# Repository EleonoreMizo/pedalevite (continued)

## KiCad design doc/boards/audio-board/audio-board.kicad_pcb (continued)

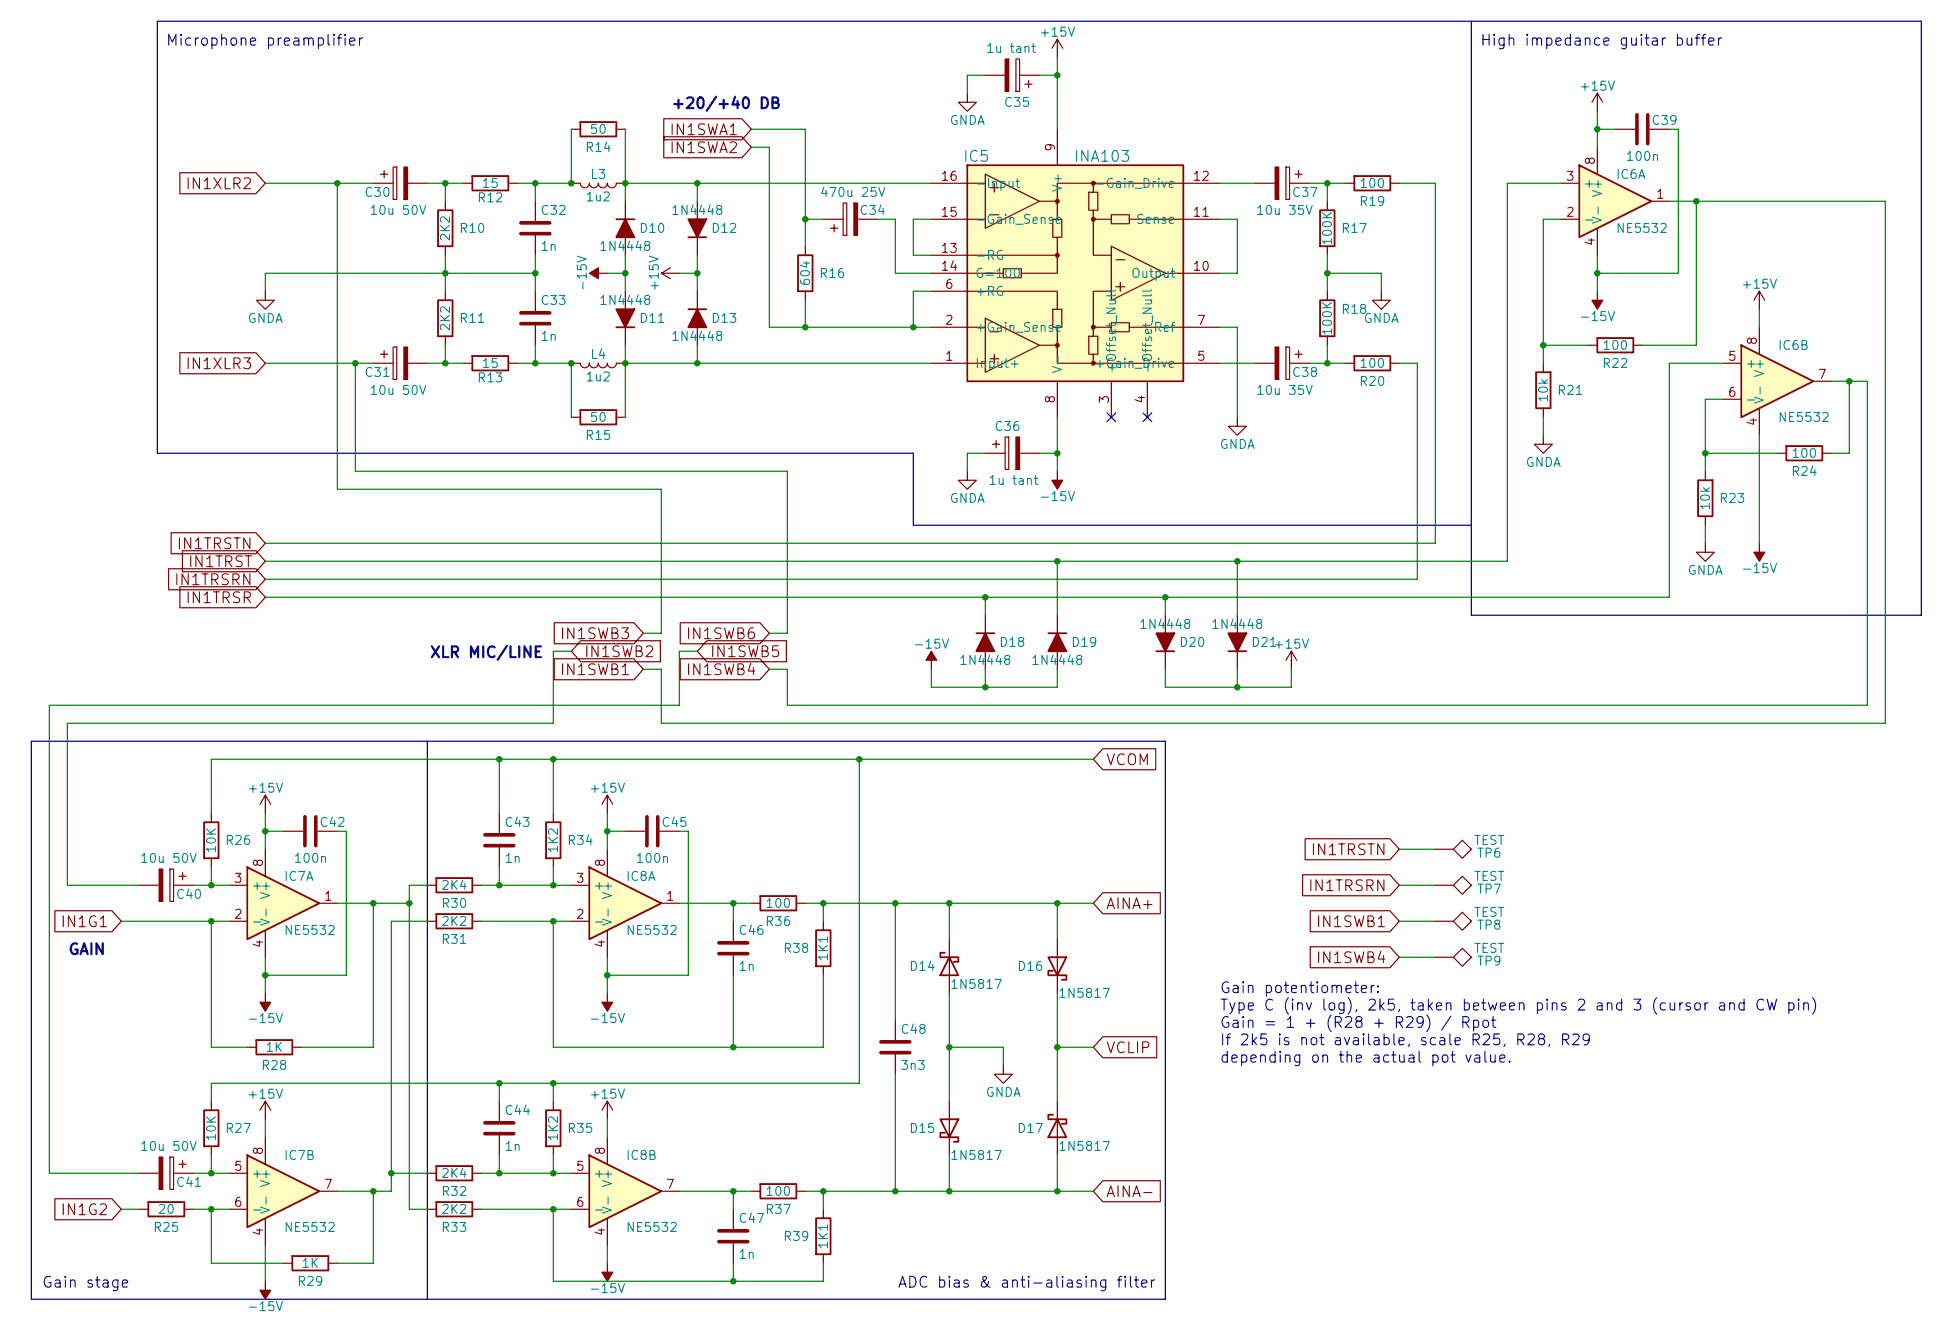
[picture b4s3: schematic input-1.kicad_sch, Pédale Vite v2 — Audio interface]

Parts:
C30, C31, C40, C41: 10u 50V; CP_Radial_D8.0mm_P3.50mm
C32, C33: 1n; C_Rect_L7.2mm_W4.5mm_P5.00mm_FKS2_FKP2_MKS2_MKP2
C34: 470u 25V; CP_Radial_D10.0mm_P5.00mm
C35, C36: 1u tant; CP_Radial_D5.0mm_P2.50mm
C37, C38: 10u 35V; CP_Radial_D5.0mm_P2.00mm
C39, C42, C45: 100n; C_Disc_D3.4mm_W2.1mm_P2.50mm
C43, C44, C46, C47: 1n; C_Disc_D6.0mm_W2.5mm_P5.00mm
C48: 3n3; C_Disc_D6.0mm_W2.5mm_P5.00mm
D10, D11, D12, D13, D18, D19, D20, D21: 1N4448; D_DO-35_SOD27_P7.62mm_Horizontal
D14, D15, D16, D17: 1N5817; D_DO-35_SOD27_P7.62mm_Horizontal
IC5: INA103; DIP-16_W7.62mm_Socket
IC6, IC7, IC8: NE5532; DIP-8_W7.62mm_Socket
L3, L4: 1u2; R_Axial_DIN0309_L9.0mm_D3.2mm_P5.08mm_Vertical
R10, R11, R31, R33: 2K2; R_Axial_DIN0207_L6.3mm_D2.5mm_P7.62mm_Horizontal
R12, R13: 15; R_Axial_DIN0207_L6.3mm_D2.5mm_P7.62mm_Horizontal
R14, R15: 50; R_Axial_DIN0207_L6.3mm_D2.5mm_P7.62mm_Horizontal
R16: 604; R_Axial_DIN0207_L6.3mm_D2.5mm_P7.62mm_Horizontal
R17, R18: 100K; R_Axial_DIN0207_L6.3mm_D2.5mm_P7.62mm_Horizontal
R19, R20, R22, R24, R36, R37: 100; R_Axial_DIN0207_L6.3mm_D2.5mm_P7.62mm_Horizontal
R21, R23: 10k; R_Axial_DIN0207_L6.3mm_D2.5mm_P7.62mm_Horizontal
R25: 20; R_Axial_DIN0207_L6.3mm_D2.5mm_P7.62mm_Horizontal
R26, R27: 10K; R_Axial_DIN0207_L6.3mm_D2.5mm_P7.62mm_Horizontal
R28, R29: 1K; R_Axial_DIN0207_L6.3mm_D2.5mm_P7.62mm_Horizontal
R30, R32: 2K4; R_Axial_DIN0207_L6.3mm_D2.5mm_P7.62mm_Horizontal
R34, R35: 1K2; R_Axial_DIN0207_L6.3mm_D2.5mm_P7.62mm_Horizontal
R38, R39: 1K1; R_Axial_DIN0207_L6.3mm_D2.5mm_P7.62mm_Horizontal
TP6, TP7, TP8, TP9: TEST; Measurement_Point_Round-TH_Small

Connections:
-15V: C36.2, C39.2, C42.2, C45.2, D10.2 (A), D11.2 (A), D18.2 (A), D19.2 (A), IC5.8 (V-), IC6.4 (V-), IC7.4 (V-), IC8.4 (V-); also elsewhere on the board
AINA+: C48.1, D14.1 (K), D16.2 (A), R36.1, R38.1; also elsewhere on the board
AINA-: C48.2, D15.1 (K), D17.2 (A), R37.1, R39.1; also elsewhere on the board
GNDA: C32.2, C33.1, C35.2, C36.1, D14.2 (A), D15.2 (A), IC5.7 (Ref), R10.2, R11.1, R17.2, R18.1, R21.1, R23.1; also elsewhere on the board
IN1G1: IC7.2 (-), R28.2; also elsewhere on the board
IN1G2: R25.2; also elsewhere on the board
IN1SWA1: C34.1, R16.1; also elsewhere on the board
IN1SWA2: IC5.2 (+Gain_Sense), IC5.6 (+RG), R16.2; also elsewhere on the board
IN1SWB1: IC6.1, R22.1, TP8.1; also elsewhere on the board
IN1SWB2: C40.2; also elsewhere on the board
IN1SWB3: C30.1; also elsewhere on the board
IN1SWB4: IC6.7, R24.1, TP9.1; also elsewhere on the board
IN1SWB5: C41.2; also elsewhere on the board
IN1SWB6: C31.1; also elsewhere on the board
IN1TRSR: D18.1 (K), D20.2 (A), IC6.5 (+); also elsewhere on the board
IN1TRSRN: R20.1, TP7.1; also elsewhere on the board
IN1TRST: D19.1 (K), D21.2 (A), IC6.3 (+); also elsewhere on the board
IN1TRSTN: R19.1, TP6.1; also elsewhere on the board
unnamed: C30.2, R10.1, R12.2
unnamed: C31.2, R11.2, R13.2
unnamed: C32.1, L3.2, R12.1, R14.2
unnamed: C33.2, L4.2, R13.1, R15.2
unnamed: C34.2, IC5.14 (G=100)
unnamed: C37.1, R17.1, R19.2
unnamed: C37.2, IC5.12 (-Gain_Drive)
unnamed: C38.1, R18.2, R20.2
unnamed: C38.2, IC5.5 (+Gain_Drive)
unnamed: C40.1, IC7.3 (+), R26.2
unnamed: C41.1, IC7.5 (+), R27.2
unnamed: C43.2, IC8.3 (+), R30.1, R34.2
unnamed: C44.2, IC8.5 (+), R32.1, R35.2
unnamed: C46.1, IC8.1, R36.2
unnamed: C46.2, IC8.2 (-), R31.1, R38.2
unnamed: C47.1, IC8.7, R37.2
unnamed: C47.2, IC8.6 (-), R33.1, R39.2
unnamed: D10.1 (K), D12.2 (A), IC5.16 (-Input), L3.1, R14.1
unnamed: D11.1 (K), D13.2 (A), IC5.1 (Input+), L4.1, R15.1
unnamed: IC5.10 (Output), IC5.11 (Sense)
unnamed: IC5.13 (-RG), IC5.15 (-Gain_Sense)
unnamed: IC6.2 (-), R21.2, R22.2
unnamed: IC6.6 (-), R23.2, R24.2
unnamed: IC7.1, R28.1, R30.2, R33.2
unnamed: IC7.6 (-), R25.1, R29.2
unnamed: IC7.7, R29.1, R31.2, R32.2
VCLIP: D16.1 (K), D17.1 (K); also elsewhere on the board
VCOM: C43.1, C44.1, R26.1, R27.1, R34.1, R35.1; also elsewhere on the board

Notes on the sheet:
High impedance guitar buffer
Gain stage
+20/+40 DB
XLR MIC/LINE
Gain potentiometer: Type C (inv log), 2k5, taken between pins 2 and 3 (cursor and CW pin) Gain = 1 + (R28 + R29) / Rpot If 2k5 is not available, scale R25, R28, R29 depending on the actual pot value.
Microphone preamplifier
ADC bias & anti-aliasing filter
GAIN

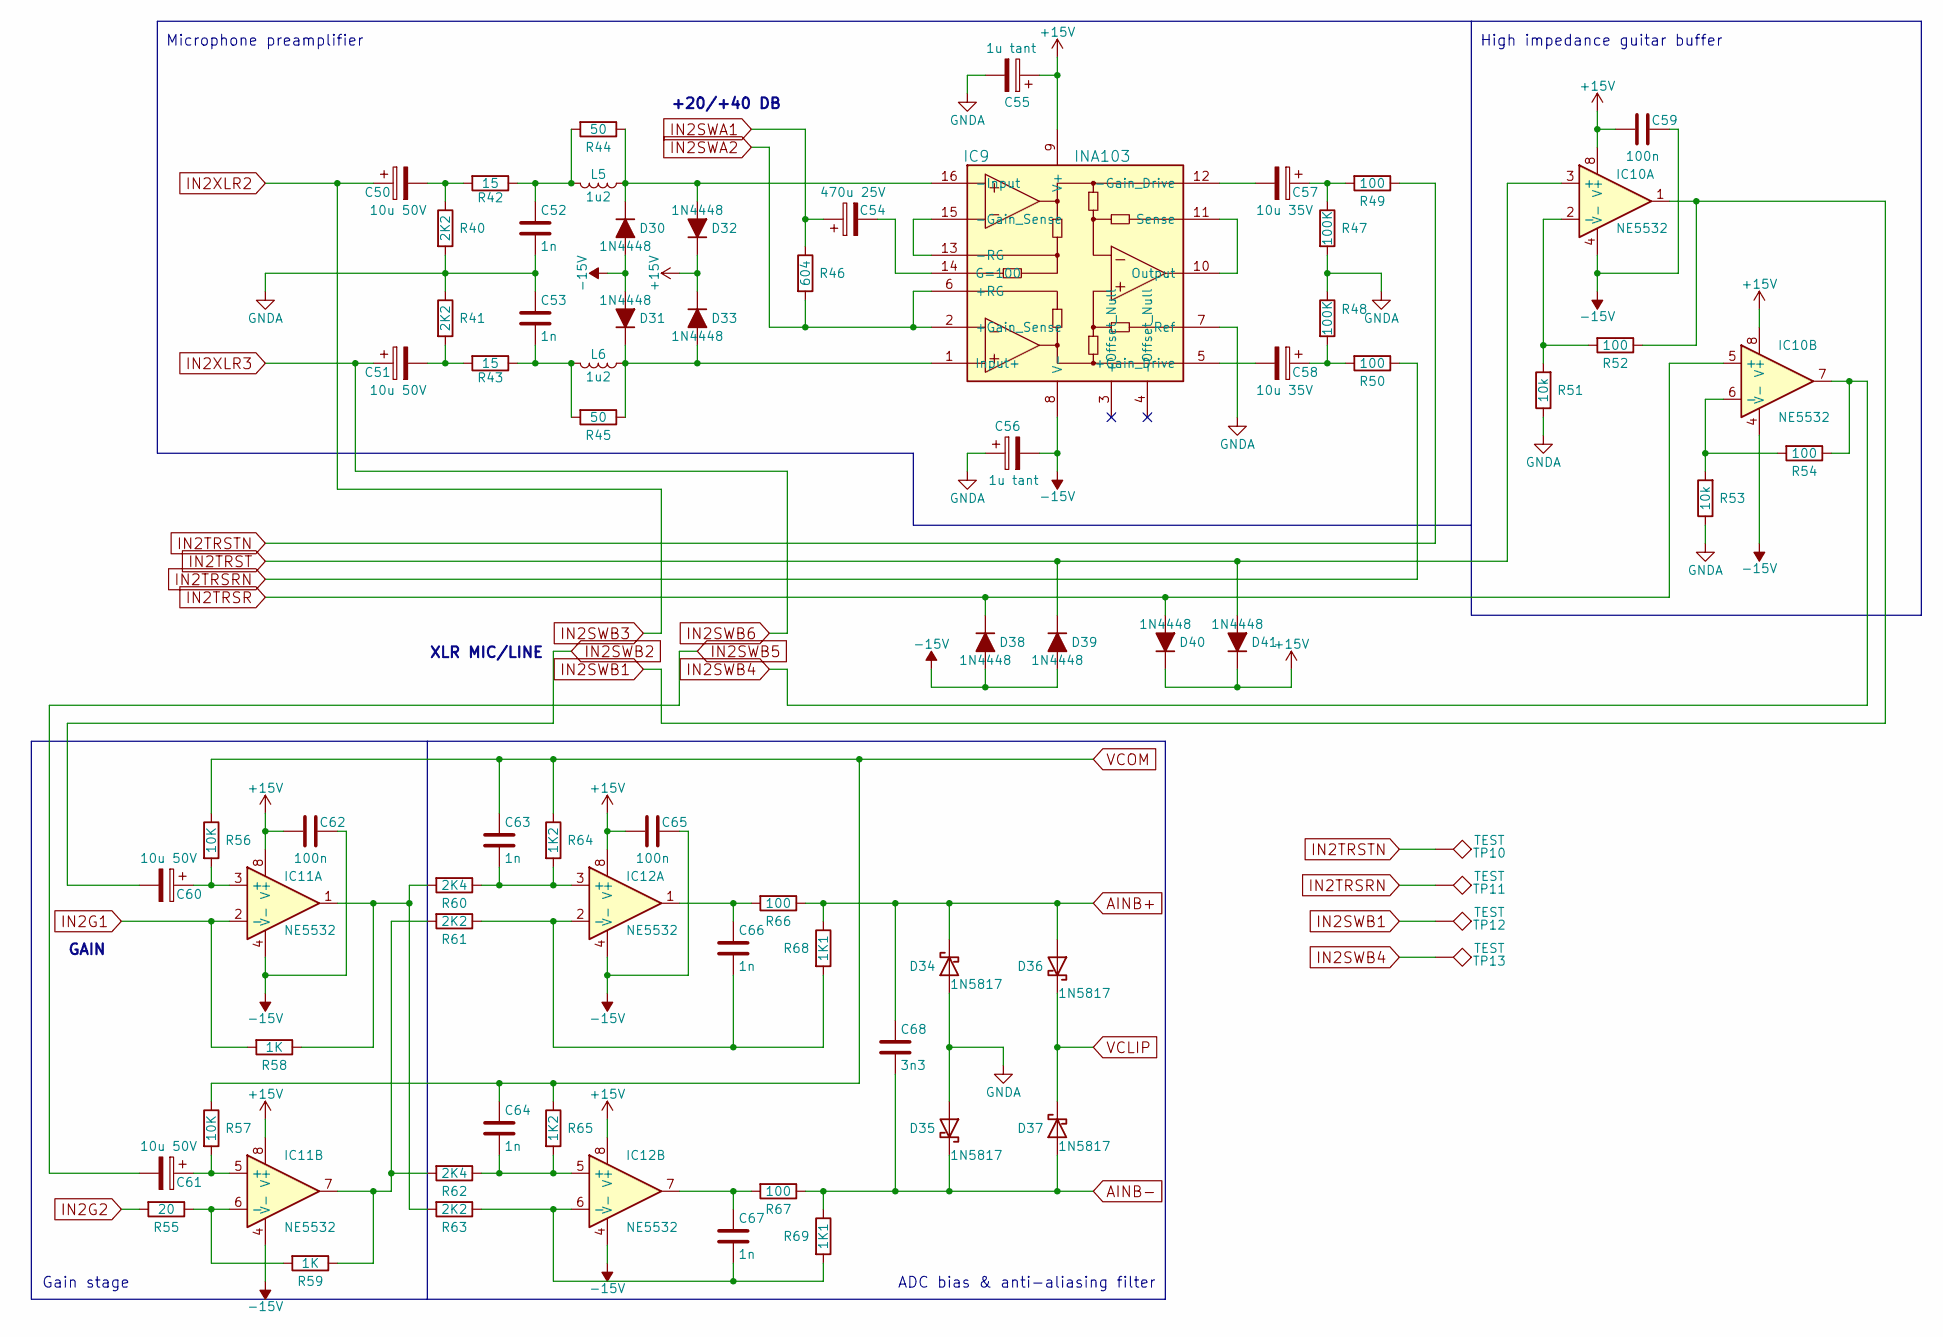
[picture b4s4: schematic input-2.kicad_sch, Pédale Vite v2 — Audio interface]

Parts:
C50, C51, C60, C61: 10u 50V; CP_Radial_D8.0mm_P3.50mm
C52, C53: 1n; C_Rect_L7.2mm_W4.5mm_P5.00mm_FKS2_FKP2_MKS2_MKP2
C54: 470u 25V; CP_Radial_D10.0mm_P5.00mm
C55, C56: 1u tant; CP_Radial_D5.0mm_P2.50mm
C57, C58: 10u 35V; CP_Radial_D5.0mm_P2.00mm
C59, C62, C65: 100n; C_Disc_D3.4mm_W2.1mm_P2.50mm
C63, C64, C66, C67: 1n; C_Disc_D6.0mm_W2.5mm_P5.00mm
C68: 3n3; C_Disc_D6.0mm_W2.5mm_P5.00mm
D30, D31, D32, D33, D38, D39, D40, D41: 1N4448; D_DO-35_SOD27_P7.62mm_Horizontal
D34, D35, D36, D37: 1N5817; D_DO-35_SOD27_P7.62mm_Horizontal
IC9: INA103; DIP-16_W7.62mm_Socket
IC10, IC11, IC12: NE5532; DIP-8_W7.62mm_Socket
L5, L6: 1u2; R_Axial_DIN0309_L9.0mm_D3.2mm_P5.08mm_Vertical
R40, R41, R61, R63: 2K2; R_Axial_DIN0207_L6.3mm_D2.5mm_P7.62mm_Horizontal
R42, R43: 15; R_Axial_DIN0207_L6.3mm_D2.5mm_P7.62mm_Horizontal
R44, R45: 50; R_Axial_DIN0207_L6.3mm_D2.5mm_P7.62mm_Horizontal
R46: 604; R_Axial_DIN0207_L6.3mm_D2.5mm_P7.62mm_Horizontal
R47, R48: 100K; R_Axial_DIN0207_L6.3mm_D2.5mm_P7.62mm_Horizontal
R49, R50, R52, R54, R66, R67: 100; R_Axial_DIN0207_L6.3mm_D2.5mm_P7.62mm_Horizontal
R51, R53: 10k; R_Axial_DIN0207_L6.3mm_D2.5mm_P7.62mm_Horizontal
R55: 20; R_Axial_DIN0207_L6.3mm_D2.5mm_P7.62mm_Horizontal
R56, R57: 10K; R_Axial_DIN0207_L6.3mm_D2.5mm_P7.62mm_Horizontal
R58, R59: 1K; R_Axial_DIN0207_L6.3mm_D2.5mm_P7.62mm_Horizontal
R60, R62: 2K4; R_Axial_DIN0207_L6.3mm_D2.5mm_P7.62mm_Horizontal
R64, R65: 1K2; R_Axial_DIN0207_L6.3mm_D2.5mm_P7.62mm_Horizontal
R68, R69: 1K1; R_Axial_DIN0207_L6.3mm_D2.5mm_P7.62mm_Horizontal
TP10, TP11, TP12, TP13: TEST; Measurement_Point_Round-TH_Small

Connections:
-15V: C56.2, C59.2, C62.2, C65.2, D30.2 (A), D31.2 (A), D38.2 (A), D39.2 (A), IC9.8 (V-), IC10.4 (V-), IC11.4 (V-), IC12.4 (V-); also elsewhere on the board
AINB+: C68.1, D34.1 (K), D36.2 (A), R66.1, R68.1; also elsewhere on the board
AINB-: C68.2, D35.1 (K), D37.2 (A), R67.1, R69.1; also elsewhere on the board
GNDA: C52.2, C53.1, C55.2, C56.1, D34.2 (A), D35.2 (A), IC9.7 (Ref), R40.2, R41.1, R47.2, R48.1, R51.1, R53.1; also elsewhere on the board
IN2G1: IC11.2 (-), R58.2; also elsewhere on the board
IN2G2: R55.2; also elsewhere on the board
IN2SWA1: C54.1, R46.1; also elsewhere on the board
IN2SWA2: IC9.2 (+Gain_Sense), IC9.6 (+RG), R46.2; also elsewhere on the board
IN2SWB1: IC10.1, R52.1, TP12.1; also elsewhere on the board
IN2SWB2: C60.2; also elsewhere on the board
IN2SWB3: C50.1; also elsewhere on the board
IN2SWB4: IC10.7, R54.1, TP13.1; also elsewhere on the board
IN2SWB5: C61.2; also elsewhere on the board
IN2SWB6: C51.1; also elsewhere on the board
IN2TRSR: D38.1 (K), D40.2 (A), IC10.5 (+); also elsewhere on the board
IN2TRSRN: R50.1, TP11.1; also elsewhere on the board
IN2TRST: D39.1 (K), D41.2 (A), IC10.3 (+); also elsewhere on the board
IN2TRSTN: R49.1, TP10.1; also elsewhere on the board
unnamed: C50.2, R40.1, R42.2
unnamed: C51.2, R41.2, R43.2
unnamed: C52.1, L5.2, R42.1, R44.2
unnamed: C53.2, L6.2, R43.1, R45.2
unnamed: C54.2, IC9.14 (G=100)
unnamed: C57.1, R47.1, R49.2
unnamed: C57.2, IC9.12 (-Gain_Drive)
unnamed: C58.1, R48.2, R50.2
unnamed: C58.2, IC9.5 (+Gain_Drive)
unnamed: C60.1, IC11.3 (+), R56.2
unnamed: C61.1, IC11.5 (+), R57.2
unnamed: C63.2, IC12.3 (+), R60.1, R64.2
unnamed: C64.2, IC12.5 (+), R62.1, R65.2
unnamed: C66.1, IC12.1, R66.2
unnamed: C66.2, IC12.2 (-), R61.1, R68.2
unnamed: C67.1, IC12.7, R67.2
unnamed: C67.2, IC12.6 (-), R63.1, R69.2
unnamed: D30.1 (K), D32.2 (A), IC9.16 (-Input), L5.1, R44.1
unnamed: D31.1 (K), D33.2 (A), IC9.1 (Input+), L6.1, R45.1
unnamed: IC9.10 (Output), IC9.11 (Sense)
unnamed: IC9.13 (-RG), IC9.15 (-Gain_Sense)
unnamed: IC10.2 (-), R51.2, R52.2
unnamed: IC10.6 (-), R53.2, R54.2
unnamed: IC11.1, R58.1, R60.2, R63.2
unnamed: IC11.6 (-), R55.1, R59.2
unnamed: IC11.7, R59.1, R61.2, R62.2
VCLIP: D36.1 (K), D37.1 (K); also elsewhere on the board
VCOM: C63.1, C64.1, R56.1, R57.1, R64.1, R65.1; also elsewhere on the board

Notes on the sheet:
ADC bias & anti-aliasing filter
Gain stage
High impedance guitar buffer
Microphone preamplifier
XLR MIC/LINE
GAIN
+20/+40 DB

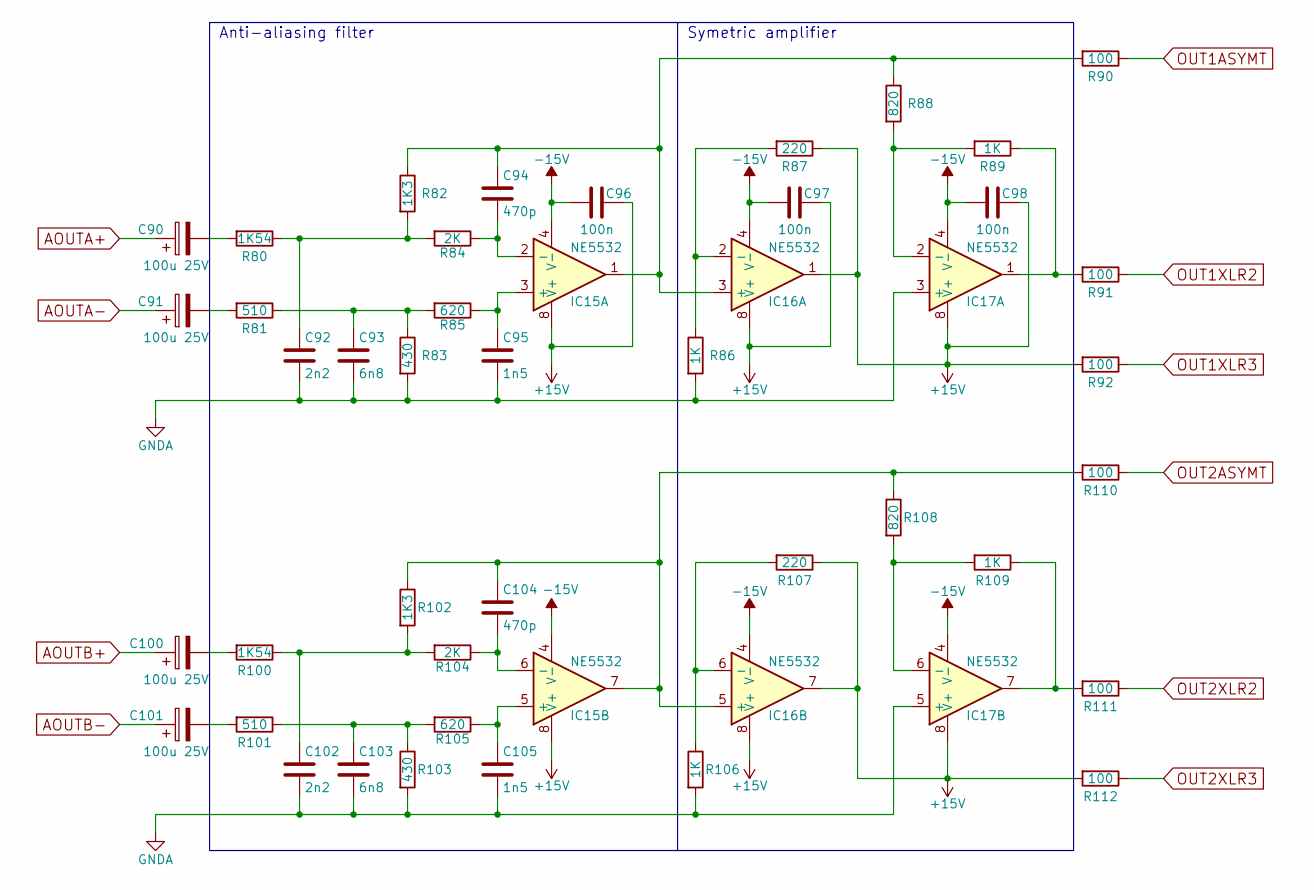
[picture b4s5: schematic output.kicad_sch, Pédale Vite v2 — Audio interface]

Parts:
C90, C91, C100, C101: 100u 25V; CP_Radial_D10.0mm_P5.00mm
C92, C102: 2n2; C_Disc_D6.0mm_W2.5mm_P5.00mm
C93, C103: 6n8; C_Disc_D6.0mm_W2.5mm_P5.00mm
C94, C104: 470p; C_Disc_D6.0mm_W2.5mm_P5.00mm
C95, C105: 1n5; C_Disc_D6.0mm_W2.5mm_P5.00mm
C96, C97, C98: 100n; C_Disc_D3.4mm_W2.1mm_P2.50mm
IC15, IC16, IC17: NE5532; DIP-8_W7.62mm_Socket
R80, R100: 1K54; R_Axial_DIN0207_L6.3mm_D2.5mm_P7.62mm_Horizontal
R81, R101: 510; R_Axial_DIN0207_L6.3mm_D2.5mm_P7.62mm_Horizontal
R82, R102: 1K3; R_Axial_DIN0207_L6.3mm_D2.5mm_P7.62mm_Horizontal
R83, R103: 430; R_Axial_DIN0207_L6.3mm_D2.5mm_P7.62mm_Horizontal
R84, R104: 2K; R_Axial_DIN0207_L6.3mm_D2.5mm_P7.62mm_Horizontal
R85, R105: 620; R_Axial_DIN0207_L6.3mm_D2.5mm_P7.62mm_Horizontal
R86, R89, R106, R109: 1K; R_Axial_DIN0207_L6.3mm_D2.5mm_P7.62mm_Horizontal
R87, R107: 220; R_Axial_DIN0207_L6.3mm_D2.5mm_P7.62mm_Horizontal
R88, R108: 820; R_Axial_DIN0207_L6.3mm_D2.5mm_P7.62mm_Horizontal
R90, R91, R92, R110, R111, R112: 100; R_Axial_DIN0207_L6.3mm_D2.5mm_P7.62mm_Horizontal

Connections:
-15V: C96.1, C97.1, C98.1, IC15.4 (V-), IC16.4 (V-), IC17.4 (V-); also elsewhere on the board
AOUTA+: C90.1; also elsewhere on the board
AOUTA-: C91.1; also elsewhere on the board
AOUTB+: C100.1; also elsewhere on the board
AOUTB-: C101.1; also elsewhere on the board
GNDA: C92.2, C93.2, C95.2, C102.2, C103.2, C105.2, IC17.3 (+), IC17.5 (+), R83.2, R86.2, R103.2, R106.2; also elsewhere on the board
unnamed: C90.2, R80.2
unnamed: C91.2, R81.2
unnamed: C92.1, R80.1, R82.2, R84.2
unnamed: C93.1, R81.1, R83.1, R85.2
unnamed: C94.1, IC15.1, IC16.3 (+), R82.1, R88.1, R90.2
unnamed: C94.2, IC15.2 (-), R84.1
unnamed: C95.1, IC15.3 (+), R85.1
unnamed: C100.2, R100.2
unnamed: C101.2, R101.2
unnamed: C102.1, R100.1, R102.2, R104.2
unnamed: C103.1, R101.1, R103.1, R105.2
unnamed: C104.1, IC15.7, IC16.5 (+), R102.1, R108.1, R110.2
unnamed: C104.2, IC15.6 (-), R104.1
unnamed: C105.1, IC15.5 (+), R105.1
unnamed: IC16.2 (-), R86.1, R87.2
unnamed: IC16.6 (-), R106.1, R107.2
unnamed: IC17.1, R89.1, R91.2
unnamed: IC17.2 (-), R88.2, R89.2
unnamed: IC17.6 (-), R108.2, R109.2
unnamed: IC17.7, R109.1, R111.2
OUT1ASYMT: R90.1; also elsewhere on the board
OUT1XLR2: R91.1; also elsewhere on the board
OUT1XLR3: R92.1; also elsewhere on the board
OUT2ASYMT: R110.1; also elsewhere on the board
OUT2XLR2: R111.1; also elsewhere on the board
OUT2XLR3: R112.1; also elsewhere on the board

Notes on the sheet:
Anti-aliasing filter
Symetric amplifier

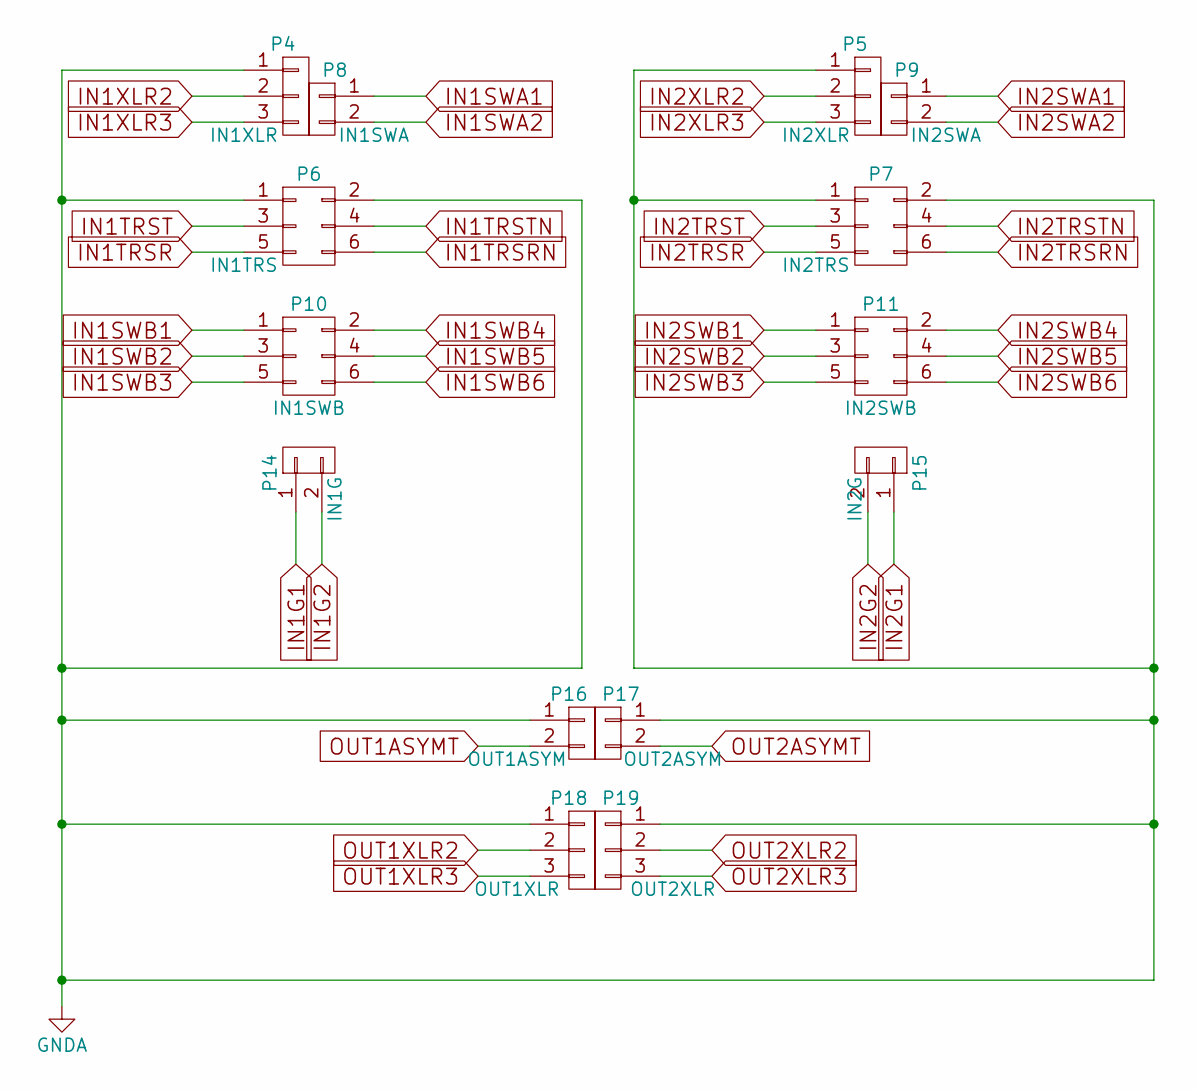
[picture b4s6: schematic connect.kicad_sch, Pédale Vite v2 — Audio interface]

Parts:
P4: IN1XLR; Pin_Header_Straight_1x03_Pitch2.54mm
P5: IN2XLR; Pin_Header_Straight_1x03_Pitch2.54mm
P6: IN1TRS; Pin_Header_Straight_2x03_Pitch2.54mm
P7: IN2TRS; Pin_Header_Straight_2x03_Pitch2.54mm
P8: IN1SWA; Pin_Header_Straight_1x02_Pitch2.54mm
P9: IN2SWA; Pin_Header_Straight_1x02_Pitch2.54mm
P10: IN1SWB; Pin_Header_Straight_2x03_Pitch2.54mm
P11: IN2SWB; Pin_Header_Straight_2x03_Pitch2.54mm
P14: IN1G; Pin_Header_Straight_1x02_Pitch2.54mm
P15: IN2G; Pin_Header_Straight_1x02_Pitch2.54mm
P16: OUT1ASYM; Pin_Header_Straight_1x02_Pitch2.54mm
P17: OUT2ASYM; Pin_Header_Straight_1x02_Pitch2.54mm
P18: OUT1XLR; Pin_Header_Straight_1x03_Pitch2.54mm
P19: OUT2XLR; Pin_Header_Straight_1x03_Pitch2.54mm

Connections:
GNDA: P4.1, P5.1, P6.1, P6.2, P7.1, P7.2, P16.1, P17.1, P18.1, P19.1; also elsewhere on the board
IN1G1: P14.1; also elsewhere on the board
IN1G2: P14.2; also elsewhere on the board
IN1SWA1: P8.1; also elsewhere on the board
IN1SWA2: P8.2; also elsewhere on the board
IN1SWB1: P10.1; also elsewhere on the board
IN1SWB2: P10.3; also elsewhere on the board
IN1SWB3: P4.2, P10.5; also elsewhere on the board
IN1SWB4: P10.2; also elsewhere on the board
IN1SWB5: P10.4; also elsewhere on the board
IN1SWB6: P4.3, P10.6; also elsewhere on the board
IN1TRSR: P6.5; also elsewhere on the board
IN1TRSRN: P6.6; also elsewhere on the board
IN1TRST: P6.3; also elsewhere on the board
IN1TRSTN: P6.4; also elsewhere on the board
IN2G1: P15.1; also elsewhere on the board
IN2G2: P15.2; also elsewhere on the board
IN2SWA1: P9.1; also elsewhere on the board
IN2SWA2: P9.2; also elsewhere on the board
IN2SWB1: P11.1; also elsewhere on the board
IN2SWB2: P11.3; also elsewhere on the board
IN2SWB3: P5.2, P11.5; also elsewhere on the board
IN2SWB4: P11.2; also elsewhere on the board
IN2SWB5: P11.4; also elsewhere on the board
IN2SWB6: P5.3, P11.6; also elsewhere on the board
IN2TRSR: P7.5; also elsewhere on the board
IN2TRSRN: P7.6; also elsewhere on the board
IN2TRST: P7.3; also elsewhere on the board
IN2TRSTN: P7.4; also elsewhere on the board
OUT1ASYMT: P16.2; also elsewhere on the board
OUT1XLR2: P18.2; also elsewhere on the board
OUT1XLR3: P18.3; also elsewhere on the board
OUT2ASYMT: P17.2; also elsewhere on the board
OUT2XLR2: P19.2; also elsewhere on the board
OUT2XLR3: P19.3; also elsewhere on the board

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
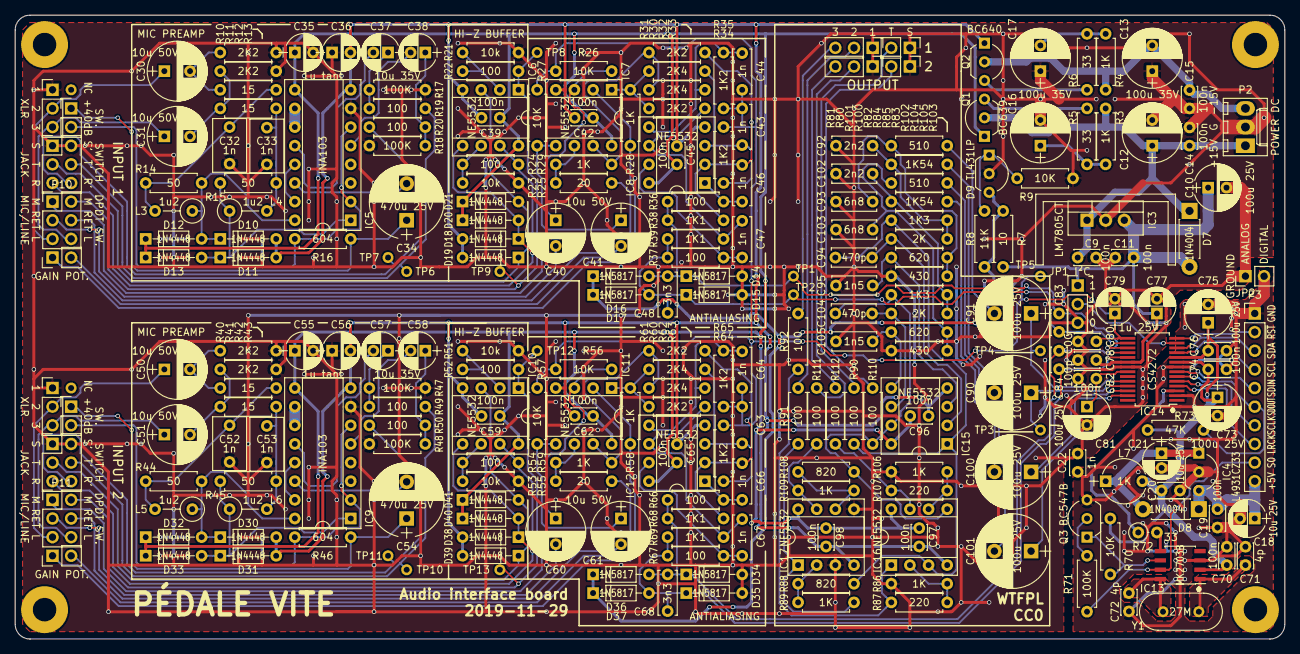
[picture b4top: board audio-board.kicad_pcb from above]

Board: 2 copper layers, 173.0 x 85.0 mm, 261 parts (0 on the bottom side), 149 nets.

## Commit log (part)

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2021-03-25 Fixed compilation errors
2021-03-26 Building doc: config and troubleshooting update
    Latest Raspberry Pi OS changed some default settings that required
    a fix.
2021-03-26 Fixed incomplete comments based on earlier versions of the BCM peripheral doc
2021-03-26 Fixed most of the I2S/DMA code
2021-03-26 Fixed most issues with channel swap
    Channels are still swapped sometimes, but this becomes rare.
2021-03-27 Removed unused variable
2021-03-27 Refined the nanosleep() test
2021-03-28 DPvabI2sDma: renamed _dma_reg to _dma_mptr for consistency
2021-04-03 Added dsp::iir::SplitMultiband + test
2021-04-03 README update
2021-04-06 dsp::dly::DelaySimple: Added R/W functions + noexcept
2021-04-06 Added dsp::iir::SplitMultibandLin + tests
2021-04-07 Added dsp::iir::OnePole4Simd (partially tested)
2021-04-07 Added dsp::iir::SplitMultibandLinSimd + test
2021-04-08 dsp::iir::SplitMultibandLin*: factorized common code
2021-04-08 Added Thiele crossover filter design
2021-04-10 Added a function to compute the group delay for a 1st-order filter
2021-04-10 Added SplitMultibandBustad
2021-04-23 Allows negative group delays
2021-04-23 fstb::ToolsSimd: added noexcept everywhere
2021-04-23 fstb::ToolsSimd: added a few functions
2021-04-23 Added SplitMultibandSimdGen + tests
2021-04-26 Added group delay calculation
2021-04-27 Extended the step list for modulation knobs
2021-04-27 Added LShift and RShift modifier keys
2021-04-27 Specified the rules for buffers
2021-04-28 TransSZBilin: added a prewarping function for roots
2021-04-28 Added dsp::fir::DesignPhaseMin + test
2021-04-28 Refined the epsilon value
2021-04-29 Fixed some compiler warnings
2021-05-02 Slight update to the skeleton plug-in
2021-05-02 Removed unused features
2021-05-02 Shortened lines with using directive
2021-05-02 Updated tag list
2021-05-03 More noexcept
2021-05-03 Added dsp::wnd::XFadeEqPowC2
2021-05-05 FrameOverlapSyn: fixed index error
2021-05-05 dsp::spec::FrameOverlap*: added reserve()
2021-05-05 Spectral Crusher: fixed FFT resolution change bug
2021-05-05 Added Spectral Freeze early prototype
2021-05-06 More atan2 approx
2021-05-08 XFadeEqPowPoly8: added a modified formula
2021-05-10 Spectral Freeze: added SIMD optimisations
2021-05-11 Simplified code + comments
2021-05-11 VolumeClone: fixed typo in parameter name
2021-05-11 Detects not-finite values at each FX input/output
2021-05-12 Fixed a few compilation errors
2021-05-12 Added tests for FFTReal and HIIR
    Most of the original test files have been included in the main
    directories, and test compilation units have been added to the
    test program.
2021-05-12 Fixed compilation warning
2021-05-15 Added speed tests and modified their display
    Switched from kilosamples per second to megasamples per second
    for high-throughput calculations
2021-05-18 OscSinCosStableSimd: changed semantics and constraints
    process_block() was taking a number of full vectors, it is now a number
    of samples. Alignments in both position and length are no more required.
2021-05-18 Removed now useless comment
2021-05-20 Plug-in factory: replaced shared_ptr with unique_ptr
2021-05-21 Effect API: added reference to host, part 1
2021-05-24 Building instructions: typos + Clang update
2021-05-24 Added Send/Return internal devices
    Allows feedback loops within the effect graph.
    Configuration file format version updated to 12.
2021-05-26 EnvFollower*: added analyse_block()
2021-05-26 Plug-in skeleton: chn_index -> chn_idx
2021-05-26 Added the Velvet Freeze effect
2021-05-27 Parameter list: unit is displayed if it fits
2021-05-28 FrameOverlapAna: added get_frame_sample()
2021-05-28 Forgot an include
2021-06-13 ToolsSimd: added ARM64 intrinsic for sum_h_flt()
2021-06-13 DelaySimple: cleaner init
2021-06-13 Added dly::RingFifo
2021-06-13 Fixed compiler warnings
2021-06-14 Enabled more compiler warnings
2021-08-02 Possible better compatibility with MacOS, untested
2021-08-02 Compilation warnings
2021-08-02 Moved rotl/rotr code to fstb common functions
2021-08-02 RndXoroshiro128p: added compatibility functions
    Can now be substituted with standard library PRNGs.
    However discard() implementation is far from optimal.
2021-08-02 Fixed compilation error
2021-08-02 Noise Bleach: filterbank improvement
    – Slightly faster and better splitting capacity.
    – Factored some code
2021-08-26 conc: fixed compatibility with OSX
2021-09-04 Added control for template specialisation
2021-10-31 conc: fixed issues with some architectures
    – Should work better on MacOS/ARM.
    – For various raisons, __atomic_compare_exchange_n() for 128-bit may not
    be lock-free on x86, even with -mcx16 compiler option. We’d better stay
    with the “legacy” builtin __sync_val_compare_and_swap() which does
    exactly what we want.
    – Armel architectures haven't any primitives guaranteed to be lock-free
2021-10-31 fstb::ToolsSimd: fixed compiler warning
2021-10-31 More hash tests
2021-10-31 Added “mid-point” parameter mapping
2021-10-31 Enforced C++14 for MSVC test project
2021-10-31 FX setup menu: fixed graphics
2021-11-16 More tanh approximations
2021-11-17 TestApprox: more reliable speed tests
2021-11-17 fstb::Approx: refactoring
    – More constexpr functions
    – Removed useless fstb:: namespace prefix
    – Replaced (a + 1) * x with a * x + x to remove the constant
    – Other misc stuff
2021-11-17 Make use of fstb::Poly
2021-11-20 fstb::Poly: added 6th and 7th-order Horner eval
    Mostly for testing and comparing with Estrin method
2021-11-20 Hypercomb: fixed stereo
2021-11-20 fstb: more log2/exp2 approximations
2021-11-21 ToolsSimd: added srli_s32() and cast_s32()
2021-11-21 Speed test for complex multiplications
2021-11-21 fstb::ToolsSimd: fixed refactoring on ARM
2021-11-22 fstb::ToolsSimd: fixed cases without SIMD
2021-11-22 More ctor for fstb::Vf32
    Allows using T(int_constant) and T(double_constant) in a template
    function without warning nor error.
2021-11-22 ToolsSimd: fixed typo in the division code
2021-11-24 Fixed compilation on ARM
2021-11-26 forgot to commit this file
2021-11-27 fstb: Moved load/store functions to Vf32
2021-11-27 fstb: Moved load/store functions to Vs32
2021-11-28 fstb: Moved compare/logical op functions to Vs32
2021-11-28 fstb::Vf32: added unary minus operator
2021-11-28 fstb: Moved some functions to Vs32 and Vf32
2021-11-29 fstb: Moved more functions to Vf32 and Vs32
2021-11-29 Fixed regression on ARM for exp2()
    Caused by commit 15ef75c94df11d83a399de0e7d927885805ab8ee
2021-11-30 fstb::Vf32: slight improvements on log2/exp2 approx
2021-11-30 TestApprox: more rigorous functional tests
    Added the possibility to set a maximum error tolerance,
    to avoid regressions and check the approximation quality
    across platforms.
2021-11-30 fstb: better rsqrt() approximation
2021-11-30 Approx: added rsqrt for Vf32
2021-12-01 TestApprox: more reliable accuracy tests
    Internal resolution was set by the type of the range boundaries,
    so specifying the test range with float would lower the resolution
    of the results when the specified type was double.
    It is now independent.
2021-12-02 fstb: added rounded-up division functions
2021-12-02 Cleaner casts
2021-12-02 Lipidipi: initial test, not concluding
2021-12-02 Make use of fstb_SIMD128_ALIGN instead of just 16
2021-12-11 Lipidipi: added band-pass voice filtering
    Reduces the flanging effect, but the sound loses fatness.
    We probably need something in-between.
2021-12-12 Lipidipi: added stereo processing
    The effect is now satisfactory and is most likely in its final shape
    on the functional level.
2021-12-13 Lipidipi: optimization for filtering
2021-12-14 Back to 16-byte alignment for ARM NEON
    Seems that 8 bytes leads to bus errors.
    But now GCC complains when alignas() argument is > 8.
    It needs more thinking about a correct way to mute the warnings.
2021-12-14 Fixed fallback for vector load/store on avr-gcc.
2021-12-14 dsp: refactored DistSlewRateLim
    Inserted a sampling-rate independent class for slew rate limiting.
2021-12-21 fstb: improved x86 detection
2021-12-21 hiir: fixed NEON implementations
2021-12-21 hiir: do while -> for
2021-12-21 hiir: optimisations for HalfBandNeon
2021-12-22 Forgot some #include
2021-12-22 hiir: optimisations for ARM NEON
2021-12-22 hiir: simplified and fixed data alignement
2021-12-23 hiir: fixed #include for some SIMD headers
2021-12-29 Slight refactoring
2022-01-01 param::TplMid: simplified and optimised formulas
2022-01-01 Backup page: check if the date is NTP-sync
2022-02-26 Typo
2022-02-27 Useless comment removal
2022-02-28 Added cycle counter register access from user land
2022-03-03 Moved PluginDetails to a separate class
2022-03-03 Forgot to adapt _rate_expected calculation
2022-03-04 Added per-effect CPU usage display
2022-03-25 FileOpWav: fixed reading for some sub-formats
    There was a mismatch between signed and unsigned types so
    negative format tags were not checked correctly.
2022-05-11 fstb: fixed the names of a few symbols
2022-05-11 fstb: added alias for aligned vectors
2022-05-11 fstb: added ULP equality tests for float
2022-05-11 fstb::Approx::cos_sin_rbj: fixed range reduction
2022-05-11 Updated board files to KiCAD 6
2022-05-29 OscSinCosStableSimd: fixed several issues
    - Initialisation and frequency changes were not handled correctly,
    leaving wrong values for scalar positions > 0.
    - correct_fast() was also buggy.
    - Moved the test into its own class.
2022-05-29 Frequency shifter helper class: clean up
    Final step for fixing several issues mainly in other classes causing
    zipper noise when processing buffers of variable length.
    Moreover the phaser delay is now taken into account for latency
    calculations.
2022-05-29 ASIO driver: added tests for variable-len proc
    Variable-length processing is disabled by default and can be enabled
    at compile-time by changing a #if.
2022-05-31 Added a wrapper for FFTReal in fixed mode
    FFTRealFixLen is faster than FFTReal but the length is fixed at compile-
    time. FFTRealRange is a wrapper around the former class, allowing the
    selection of different lengths at runtime.
    These classes might be moved in the ffft library later.
2022-05-31 Added a test for SpectralFreeze
2022-06-01 Fixed missing code + tests
2022-06-01 fstb::Approx: more tests
2022-06-01 Changed the compiler selection method
2022-06-02 SpectralFreeze: added Crystalise effect
    Experimental. Radius parameter will be probably removed.
2022-06-03 SpectralFreeze: changed thr curve for Crystalise
    Reverted an earlier modification to makes sure that the gain for the
    maximum-weight bins is never less than 1.
2022-06-03 User manual: updated Spectral Freeze description
2022-06-07 VST2 wrapper: added trace for host call
2022-06-07 fstb: added init functions for SIMD vectors
2022-06-07 Added Crystalise effect
2022-06-07 Refactoring: common FFT parameters
2022-06-08 Added definitions for static constexpr declarations
2022-06-20 Fixed compiler warnings with sizeof
2022-06-20 Alt SSE2 implementation for _mm_mullo_epi32
2022-06-28 TestApprox: type conversion rounding errors
    For the reference calculation, rounds the input value to the target
    bitdepth, so we don't start with a rounding error on the input
    operand.
2022-06-28 Building instructions: details about grounding
2022-09-21 Misc. formating
2022-09-22 Added test for mullo_epi32() emulation
2022-09-22 Test is not x86-specific
2022-11-11 Fixed the scale of a parameter change w/ shift
2022-11-15 Doc: notes about legacy RPi OS and Clang versions
2023-02-11 fstb::Approx: more exp2 formulas
2023-03-21 Double distortion: fixed density in stereo
2023-04-23 Clang: removed unsupported option
    -fexperimental-new-pass-manager is the default since Clang 13.
    The option doesn't exist in Clang 16 anymore.
2023-04-24 fstb: moved implementation details
2023-04-24 Doc: updated building instructions for Clang 15
2023-04-24 fstb: refactored get_prev_pow_2/get_next_pow_2
    Now uses __builtin_clz() on gcc-compatible compilers
2023-04-25 PEq: fixed potential "cosine problem" in display
    Not encountered so far, but better safe than sorry.
2023-04-27 Added constants for the usual GPIO pins
2023-04-27 Digit grouping for large decimal literals
2023-04-28 configure.ac: added pigpio library
    Only library check and link, no implementation yet.
    wiringPi is still the default to access the GPIO, but we'll switch
    to pigpio once properly implemented.
2023-04-29 configure.ac: fixed default for wiringPi
2023-04-29 Added missing parameter check
2023-04-30 Replaced wiringPi with a custom implementation
    Pigpio was OK for the required operations but had negative side effects
    on the audio I2S code, probably messing with the DMA or something.
    Optional support for wiringPi is kept as a backup solution, time to make
    sure everything works reliably.
